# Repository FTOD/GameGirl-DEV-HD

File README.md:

GameGirl Development version is the GameGirl with power supply only from DEBUG port and USB-C.

This design is under CERN Open Hardware Licence Version 2 - Permissive license.
Please refer to [License.txt](license.txt) and [cern_ohl_p.v2.howto.pdf](cern_ohl_p_v2_howto.pdf) for more detail.

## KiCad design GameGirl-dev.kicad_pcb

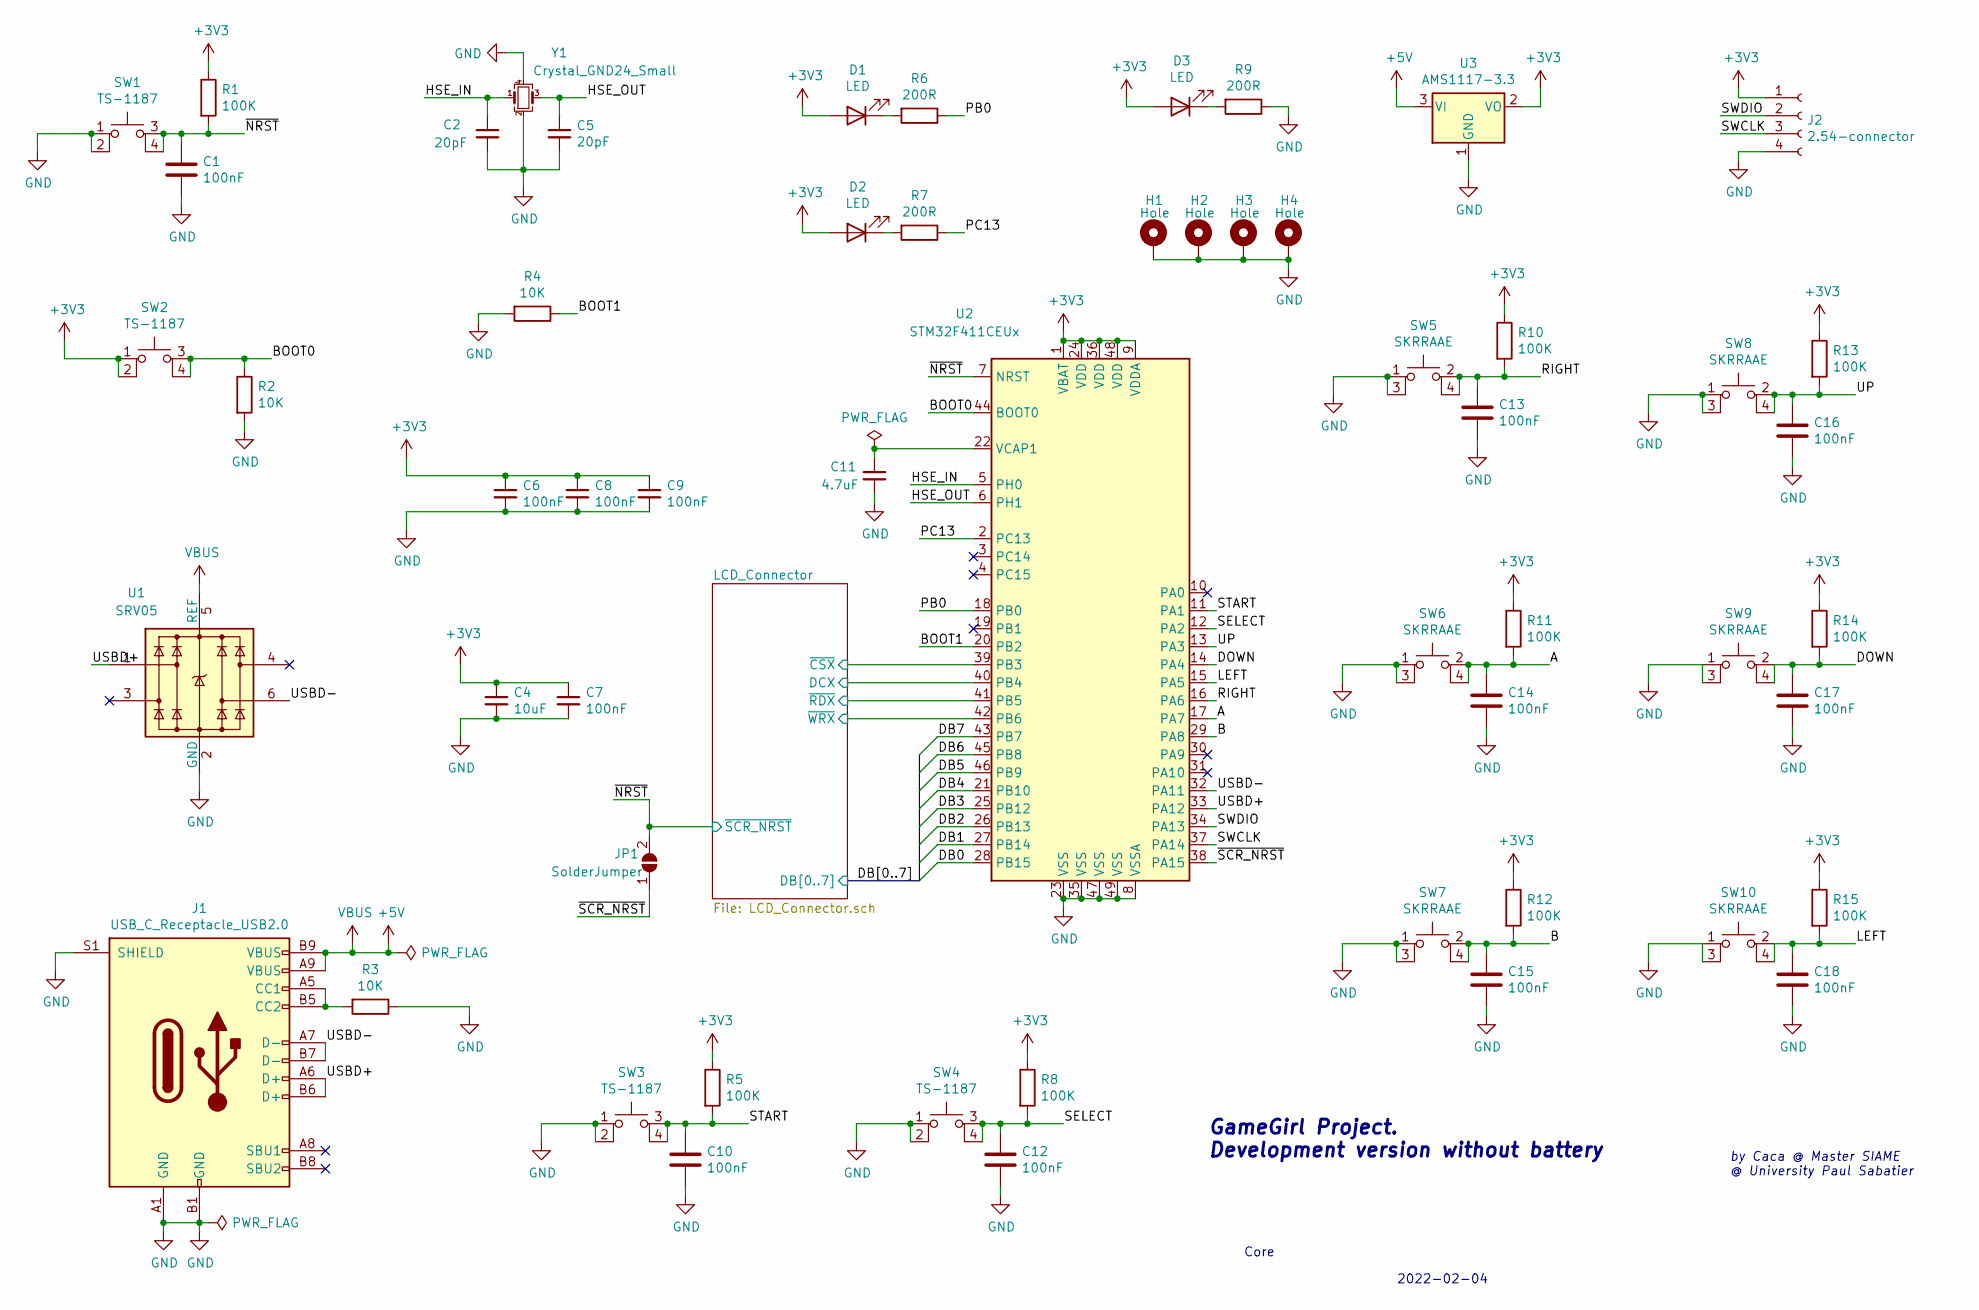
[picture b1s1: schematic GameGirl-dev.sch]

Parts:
C1, C6, C7, C8, C9, C10, C12, C13, C14, C15, C16, C17, C18: 100nF; C_0402_1005Metric
C2, C5: 20pF; C_0402_1005Metric
C4: 10uF; C_0805_2012Metric_Pad1.18x1.45mm_HandSolder
C11: 4.7uF; C_0805_2012Metric_Pad1.18x1.45mm_HandSolder
D1, D2: LED; LED_0603_1608Metric
D3: LED; LED_0805_2012Metric
H1, H2, H3, H4: Hole; MountingHole_3.2mm_M3_DIN965_Pad_TopBottom
J1: USB_C_Receptacle_USB2.0; USB_C_Receptacle_XKB_U262-16XN-4BVC11; LCSC C319148
J2: 2.54-connector; PinHeader_1x04_P2.54mm_Horizontal
JP1: SolderJumper; SolderJumper-2_P1.3mm_Open_TrianglePad1.0x1.5mm
R1, R5, R8, R10, R11, R12, R13, R14, R15: 100K; R_0402_1005Metric
R2, R3, R4: 10K; R_0402_1005Metric
R6, R7, R9: 200R; R_0402_1005Metric
SW1, SW2, SW3, SW4: TS-1187; TS1187ABAB; LCSC C318884
SW5, SW6, SW7, SW8, SW9, SW10: SKRRAAE; SKRR; LCSC C97437
U1: SRV05; SOT-23-6; LCSC C85364
U2: STM32F411CEUx; QFN-48-1EP_7x7mm_P0.5mm_EP5.6x5.6mm
U3: AMS1117-3.3; SOT-223
Y1: Crystal_GND24_Small; Crystal_SMD_3225-4Pin_3.2x2.5mm; LCSC C9006

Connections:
+3V3: C4.1, C6.1, C7.1, C8.1, C9.1, D1.2 (A), D2.2 (A), D3.2 (A), J2.1, R1.1, R5.1, R8.1, R10.1, R11.1, R12.1, R13.1, R14.1, R15.1, SW2.1 (A), SW2.2 (B), U2.1 (VBAT), U2.9 (VDDA), U2.24 (VDD), U2.36 (VDD), U2.48 (VDD), U3.2 (VO); also elsewhere on the board
+5V: J1.A4 (VBUS), J1.A9 (VBUS), J1.B4 (VBUS), J1.B9 (VBUS), U1.5 (REF), U3.3 (VI)
/A: C14.1, R11.2, SW6.2, SW6.4, U2.17 (PA7)
/B: C15.1, R12.2, SW7.2, SW7.4, U2.29 (PA8)
/BOOT0: R2.1, SW2.3 (C), SW2.4 (D), U2.44 (BOOT0)
/BOOT1: R4.1, U2.20 (PB2)
/DB0: U2.28 (PB15); also elsewhere on the board
/DB1: U2.27 (PB14); also elsewhere on the board
/DB2: U2.26 (PB13); also elsewhere on the board
/DB3: U2.25 (PB12); also elsewhere on the board
/DB4: U2.21 (PB10); also elsewhere on the board
/DB5: U2.46 (PB9); also elsewhere on the board
/DB6: U2.45 (PB8); also elsewhere on the board
/DB7: U2.43 (PB7); also elsewhere on the board
/DOWN: C17.1, R14.2, SW9.2, SW9.4, U2.14 (PA4)
/HSE_IN: C2.1, U2.5 (PH0), Y1.1
/HSE_OUT: C5.1, U2.6 (PH1), Y1.3
/LCD_Connector/DCX: U2.40 (PB4); also elsewhere on the board
/LCD_Connector/~CSX: U2.39 (PB3); also elsewhere on the board
/LCD_Connector/~RDX: U2.41 (PB5); also elsewhere on the board
/LCD_Connector/~WRX: U2.42 (PB6); also elsewhere on the board
/LEFT: C18.1, R15.2, SW10.2, SW10.4, U2.15 (PA5)
/PB0: R6.1, U2.18 (PB0)
/PC13: R7.1, U2.2 (PC13)
/RIGHT: C13.1, R10.2, SW5.2, SW5.4, U2.16 (PA6)
/SELECT: C12.1, R8.2, SW4.3 (C), SW4.4 (D), U2.12 (PA2)
/START: C10.1, R5.2, SW3.3 (C), SW3.4 (D), U2.11 (PA1)
/SWCLK: J2.3, U2.37 (PA14)
/SWDIO: J2.2, U2.34 (PA13)
/UP: C16.1, R13.2, SW8.2, SW8.4, U2.13 (PA3)
/USBD+: J1.A6 (D+), J1.B6 (D+), U1.1, U2.33 (PA12)
/USBD-: J1.A7 (D-), J1.B7 (D-), U1.6, U2.32 (PA11)
/~NRST: C1.1, JP1.2 (B), R1.2, SW1.3 (C), SW1.4 (D), U2.7 (NRST); also elsewhere on the board
/~SCR_NRST: JP1.1 (A), U2.38 (PA15)
GND: C1.2, C2.2, C4.2, C5.2, C6.2, C7.2, C8.2, C9.2, C10.2, C11.2, C12.2, C13.2, C14.2, C15.2, C16.2, C17.2, C18.2, H1.1, H2.1, H3.1, H4.1, J1.A1 (GND), J1.A12 (GND), J1.B1 (GND), J1.B12 (GND), J1.S1 (SHIELD), J2.4, R2.2, R3.1, R4.2, R9.1, SW1.1 (A), SW1.2 (B), SW3.1 (A), SW3.2 (B), SW4.1 (A), SW4.2 (B), SW5.1, SW5.3, SW6.1, SW6.3, SW7.1, SW7.3, SW8.1, SW8.3, SW9.1, SW9.3, SW10.1, SW10.3, U1.2 (GND), U2.8 (VSSA), U2.23 (VSS), U2.35 (VSS), U2.47 (VSS), U2.49 (VSS), U3.1 (GND), Y1.2, Y1.4; also elsewhere on the board
unnamed: C11.1, U2.22 (VCAP1)
unnamed: D1.1 (K), R6.2
unnamed: D2.1 (K), R7.2
unnamed: D3.1 (K), R9.2
unnamed: J1.A5 (CC1), J1.B5 (CC2), R3.2

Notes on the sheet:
GameGirl Project. Development version without battery
by Caca @ Master SIAME @ University Paul Sabatier
2022-02-04
Core

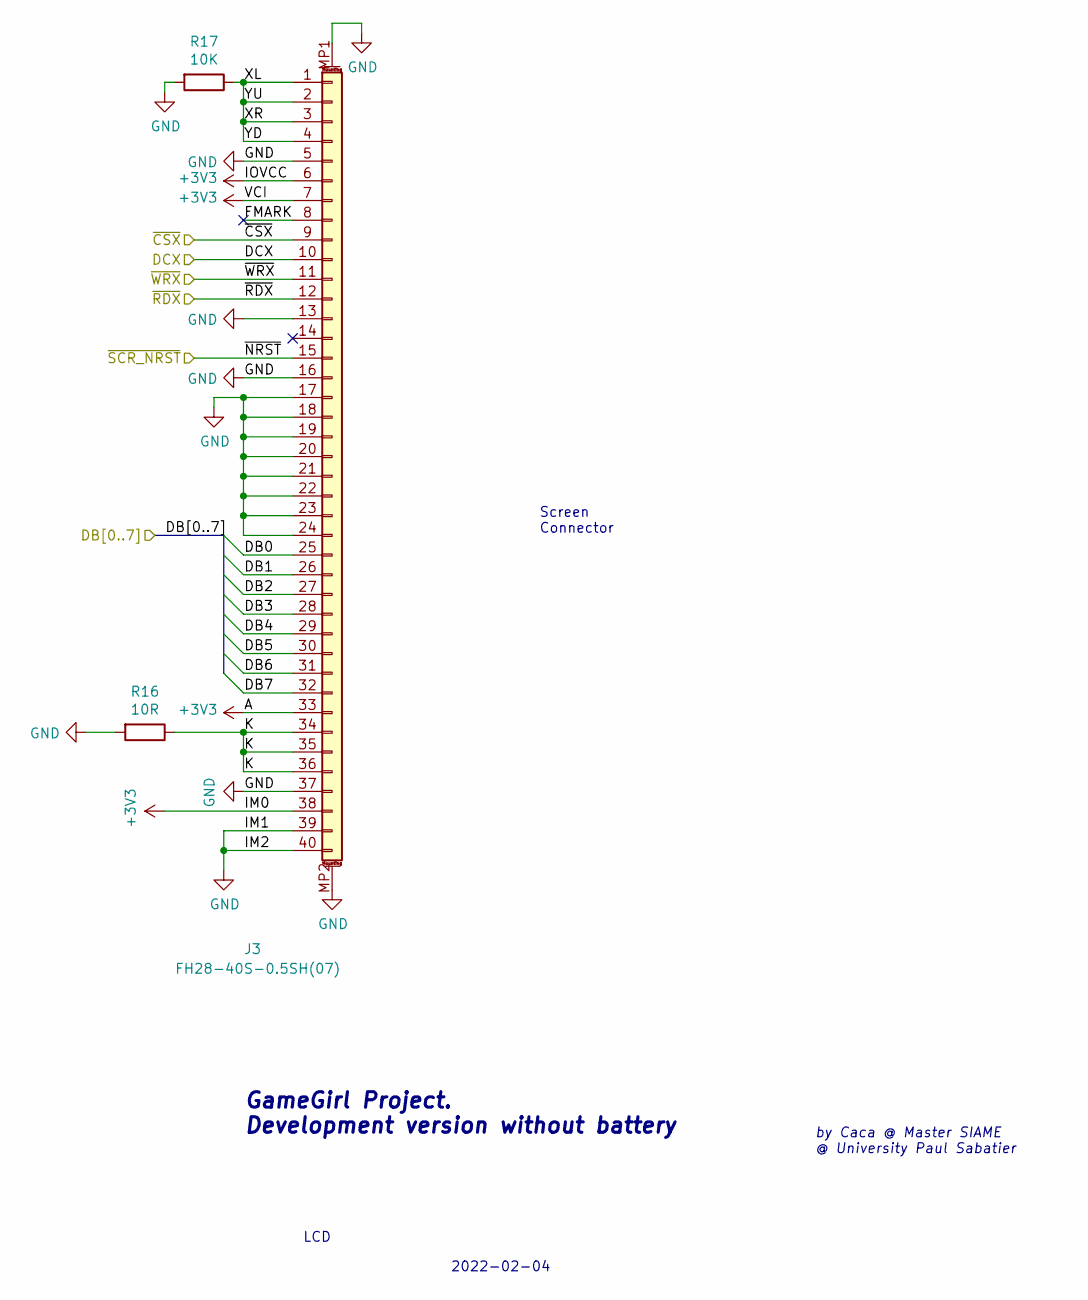
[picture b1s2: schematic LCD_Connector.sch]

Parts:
J3: FH28-40S-0.5SH(07); FH2840S05SH07; LCSC C424677
R16: 10R; R_0402_1005Metric
R17: 10K; R_0402_1005Metric

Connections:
+3V3: J3.6, J3.7, J3.33, J3.38; also elsewhere on the board
/DB0: J3.25; also elsewhere on the board
/DB1: J3.26; also elsewhere on the board
/DB2: J3.27; also elsewhere on the board
/DB3: J3.28; also elsewhere on the board
/DB4: J3.29; also elsewhere on the board
/DB5: J3.30; also elsewhere on the board
/DB6: J3.31; also elsewhere on the board
/DB7: J3.32; also elsewhere on the board
/LCD_Connector/DCX: J3.10; also elsewhere on the board
/LCD_Connector/FMARK: J3.8
/LCD_Connector/K: J3.34, J3.35, J3.36, R16.1
/LCD_Connector/XL: J3.1, J3.2, J3.3, J3.4, R17.1
/LCD_Connector/~CSX: J3.9; also elsewhere on the board
/LCD_Connector/~RDX: J3.12; also elsewhere on the board
/LCD_Connector/~WRX: J3.11; also elsewhere on the board
/~NRST: J3.15; also elsewhere on the board
GND: J3.5, J3.13, J3.16, J3.17, J3.18, J3.19, J3.20, J3.21, J3.22, J3.23, J3.24, J3.37, J3.39, J3.40, J3.MP1 (MountPin), J3.MP2 (MountPin), R16.2, R17.2; also elsewhere on the board

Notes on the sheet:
Screen Connector
GameGirl Project. Development version without battery
by Caca @ Master SIAME @ University Paul Sabatier
2022-02-04
LCD

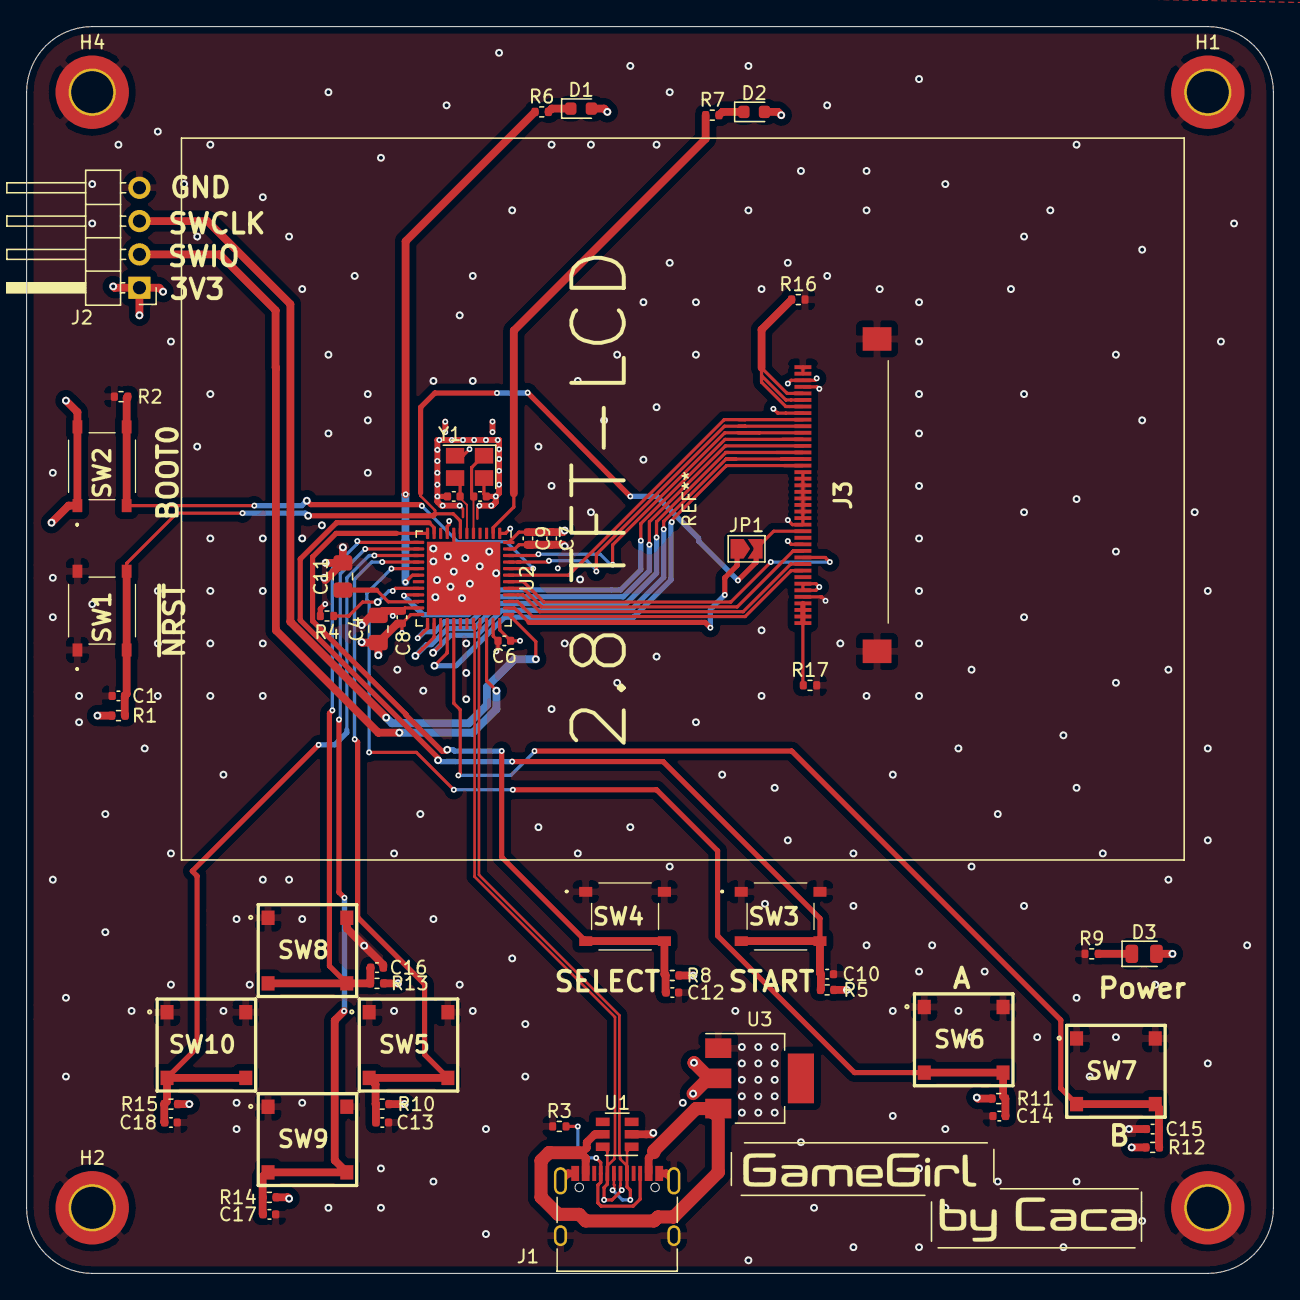
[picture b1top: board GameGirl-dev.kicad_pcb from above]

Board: 4 copper layers, 95.0 x 95.0 mm, 59 parts (0 on the bottom side), 42 nets.

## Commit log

2022-02-06 add license
2022-02-06 last modifs before fabrication
2022-02-15 add 3D model
2022-02-23 add schematic pdf, some changes to pcb
